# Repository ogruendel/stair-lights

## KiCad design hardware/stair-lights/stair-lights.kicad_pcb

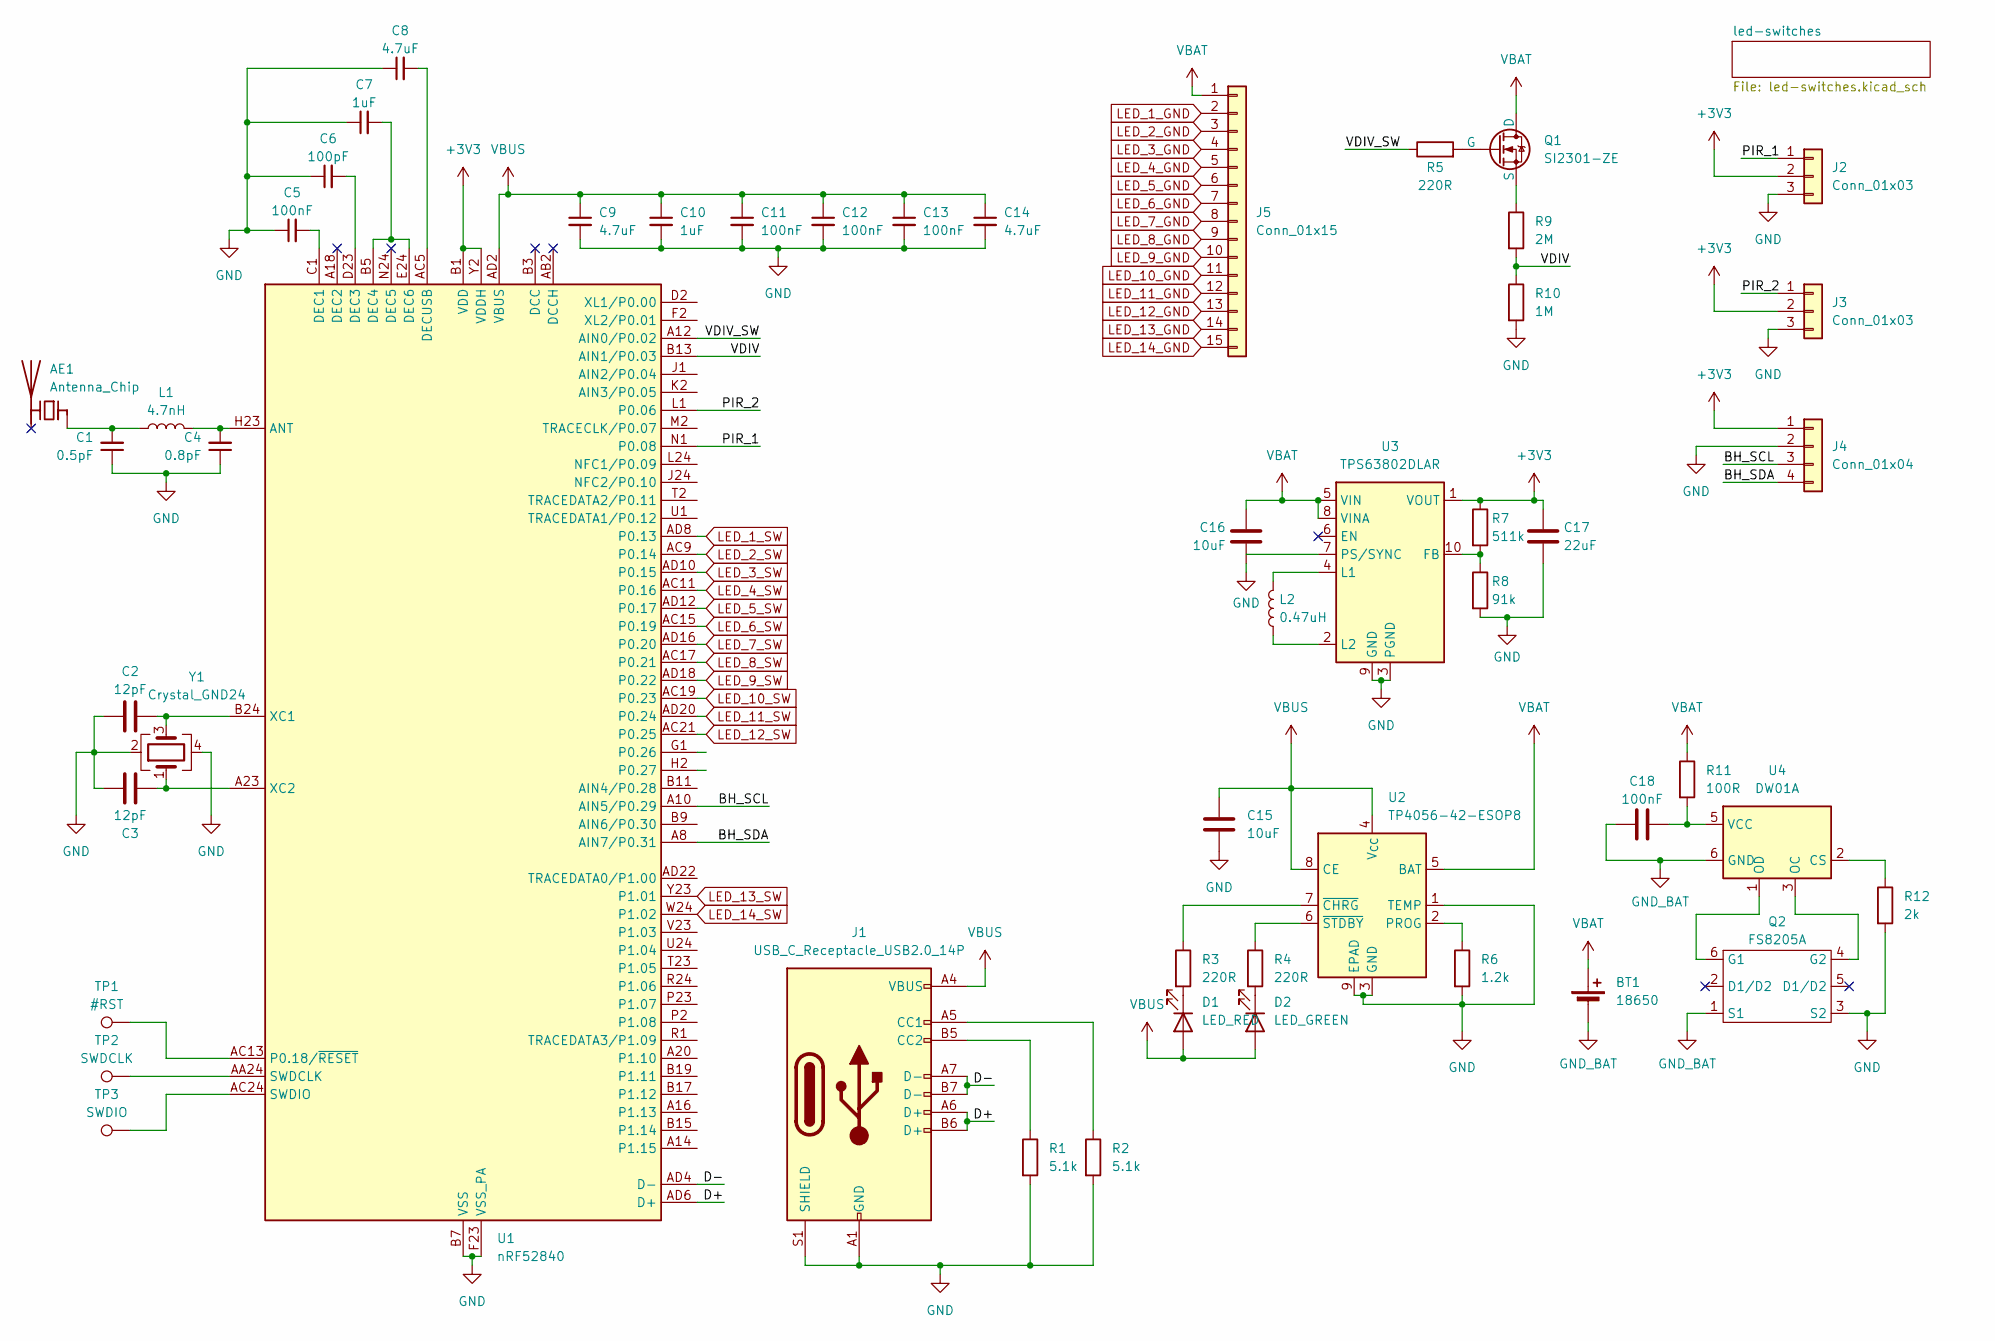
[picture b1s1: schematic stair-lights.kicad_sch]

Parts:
AE1: Antenna_Chip; L_1206_3216Metric; MPN C127629
BT1: 18650; BatteryHolder_Keystone_1042_1x18650; MPN C2988620
C1: 0.5pF; C_0402_1005Metric; MPN C285052
C2, C3: 12pF; C_0402_1005Metric; MPN C45359894
C4: 0.8pF; C_0402_1005Metric; MPN C41361068
C5, C11, C12, C13, C18: 100nF; C_0402_1005Metric; MPN C6119799
C6: 100pF; C_0402_1005Metric; MPN C77177
C7, C10: 1uF; C_0603_1608Metric; MPN C1592
C8, C9, C14: 4.7uF; C_0402_1005Metric; MPN C23733
C15, C16: 10uF; C_0603_1608Metric; MPN C6119842
C17: 22uF; C_0603_1608Metric; MPN C380323
D1: LED_RED; LED_1.7x1.1mm; MPN C965860
D2: LED_GREEN; LED_1.7x1.1mm; MPN C965863
J1: USB_C_Receptacle_USB2.0_14P; USB_C_Receptacle_GCT_USB4105-xx-A_16P_TopMnt_Horizontal; MPN C2765186
J2: Conn_01x03; JST_XH_S3B-XH-A_1x03_P2.50mm_Horizontal; MPN C157928
J3: Conn_01x03; JST_XH_B3B-XH-AM_1x03_P2.50mm_Vertical; MPN C161870
J4: Conn_01x04; JST_XH_B4B-XH-AM_1x04_P2.50mm_Vertical; MPN C161871
J5: Conn_01x15; JST_XH_S15B-XH-A_1x15_P2.50mm_Horizontal
L1: 4.7nH; L_0402_1005Metric; MPN C86065C86065
L2: 0.47uH; L_1008_2520Metric; MPN C5832368
Q1: SI2301-ZE; SOT-23; MPN C5261052
Q2: FS8205A; SOT-23-6; MPN C2830320
R1, R2: 5.1k; R_0603_1608Metric; MPN C26000
R3, R4, R5: 220R; R_0603_1608Metric; MPN C2907127
R6: 1.2k; R_0603_1608Metric; MPN C25987
R7: 511k; R_0402_1005Metric; MPN C5126239
R8: 91k; R_0402_1005Metric; MPN C4147
R9: 2M; R_0402_1005Metric; MPN C138014
R10: 1M; R_0402_1005Metric; MPN C26083
R11: 100R; R_0603_1608Metric; MPN C2907089
R12: 2k; R_0603_1608Metric; MPN C22975
TP1: #RST; TestPoint_Pad_D1.5mm
TP2: SWDCLK; TestPoint_Pad_D1.5mm
TP3: SWDIO; TestPoint_Pad_D1.5mm
U1: nRF52840; Nordic_AQFN-73-1EP_7x7mm_P0.5mm; MPN C190794
U2: TP4056-42-ESOP8; SOIC-8-1EP_3.9x4.9mm_P1.27mm_EP2.41x3.3mm_ThermalVias; MPN C7473158
U3: TPS63802DLAR; VSON-10; MPN C2845237
U4: DW01A; SOT-23-6; MPN C18164398
Y1: Crystal_GND24; Crystal_SMD_2016-4Pin_2.0x1.6mm; MPN C37635331

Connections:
+3V3: C17.2, J2.2, J3.2, J4.1, R7.1, U1.A22 (VDD), U1.AD14 (VDD), U1.AD23 (VDD), U1.B1 (VDD), U1.W1 (VDD), U1.Y2 (VDDH), U3.1 (VOUT)
/BH_SCL: J4.3, U1.A10 (AIN5/P0.29)
/BH_SDA: J4.4, U1.A8 (AIN7/P0.31)
/D+: J1.A6 (D+), J1.B6 (D+), U1.AD6 (D+)
/D-: J1.A7 (D-), J1.B7 (D-), U1.AD4 (D-)
/PIR_1: J2.1, U1.N1 (P0.08)
/PIR_2: J3.1, U1.L1 (P0.06)
/VDIV: R9.2, R10.1, U1.B13 (AIN1/P0.03)
/VDIV_SW: R5.1, U1.A12 (AIN0/P0.02)
GND: C1.1, C2.1, C3.1, C4.1, C5.1, C6.1, C7.1, C8.1, C9.2, C10.2, C11.2, C12.2, C13.2, C14.2, C15.2, C16.1, C17.1, J1.A1 (GND), J1.A12 (GND), J1.B1 (GND), J1.B12 (GND), J1.S1 (SHIELD), J2.3, J3.3, J4.2, Q2.3 (S2), R1.2, R2.2, R6.2, R8.2, R10.2, R12.2, U1.B7 (VSS), U1.EP (VSS), U1.F23 (VSS_PA), U2.1 (TEMP), U2.3 (GND), U2.9 (EPAD), U3.3 (PGND), U3.9 (GND), Y1.2, Y1.4; also elsewhere on the board
GND_BAT: BT1.2 (-), C18.1, Q2.1 (S1), U4.6 (GND)
LED_1_GND: J5.2; also elsewhere on the board
LED_1_SW: U1.AD8 (P0.13); also elsewhere on the board
LED_2_GND: J5.3; also elsewhere on the board
LED_2_SW: U1.AC9 (P0.14); also elsewhere on the board
LED_3_GND: J5.4; also elsewhere on the board
LED_3_SW: U1.AD10 (P0.15); also elsewhere on the board
LED_4_GND: J5.5; also elsewhere on the board
LED_4_SW: U1.AC11 (P0.16); also elsewhere on the board
LED_5_GND: J5.6; also elsewhere on the board
LED_5_SW: U1.AD12 (P0.17); also elsewhere on the board
LED_6_GND: J5.7; also elsewhere on the board
LED_6_SW: U1.AC15 (P0.19); also elsewhere on the board
LED_7_GND: J5.8; also elsewhere on the board
LED_7_SW: U1.AD16 (P0.20); also elsewhere on the board
LED_8_GND: J5.9; also elsewhere on the board
LED_8_SW: U1.AC17 (P0.21); also elsewhere on the board
LED_9_GND: J5.10; also elsewhere on the board
LED_9_SW: U1.AD18 (P0.22); also elsewhere on the board
LED_10_GND: J5.11; also elsewhere on the board
LED_10_SW: U1.AC19 (P0.23); also elsewhere on the board
LED_11_GND: J5.12; also elsewhere on the board
LED_11_SW: U1.AD20 (P0.24); also elsewhere on the board
LED_12_GND: J5.13; also elsewhere on the board
LED_12_SW: U1.AC21 (P0.25); also elsewhere on the board
LED_13_GND: J5.14; also elsewhere on the board
LED_13_SW: U1.Y23 (P1.01); also elsewhere on the board
LED_14_GND: J5.15; also elsewhere on the board
LED_14_SW: U1.W24 (P1.02); also elsewhere on the board
unnamed: AE1.1 (FEED), C1.2, L1.1
unnamed: D1.1 (K), R3.2
unnamed: D2.1 (K), R4.2
unnamed: J1.A5 (CC1), R2.1
unnamed: J1.B5 (CC2), R1.1
unnamed: Q1.1 (G), R5.2
unnamed: Q1.2 (S), R9.1
unnamed: Q2.6 (G1), U4.1 (OD)
unnamed: Q2.4 (G2), U4.3 (OC)
unnamed: C4.2, L1.2, U1.H23 (ANT)
unnamed: C5.2, U1.C1 (DEC1)
unnamed: C6.2, U1.D23 (DEC3)
unnamed: C7.2, U1.B5 (DEC4), U1.E24 (DEC6)
unnamed: C8.2, U1.AC5 (DECUSB)
unnamed: TP1.1, U1.AC13 (P0.18/~RESET)
unnamed: TP2.1, U1.AA24 (SWDCLK)
unnamed: TP3.1, U1.AC24 (SWDIO)
unnamed: C2.2, U1.B24 (XC1), Y1.3
unnamed: C3.2, U1.A23 (XC2), Y1.1
unnamed: R6.1, U2.2 (PROG)
unnamed: R3.1, U2.7 (~CHRG)
unnamed: R4.1, U2.6 (~STDBY)
unnamed: R7.2, R8.1, U3.10 (FB)
unnamed: L2.2, U3.4 (L1)
unnamed: L2.1, U3.2 (L2)
unnamed: R12.1, U4.2 (CS)
unnamed: C18.2, R11.2, U4.5 (VCC)
VBAT: BT1.1 (+), C16.2, J5.1, Q1.3 (D), R11.1, U2.5 (BAT), U3.5 (VIN), U3.8 (VINA)
VBUS: C9.1, C10.1, C11.1, C12.1, C13.1, C14.1, C15.1, D1.2 (A), D2.2 (A), J1.A4 (VBUS), J1.A9 (VBUS), J1.B4 (VBUS), J1.B9 (VBUS), U1.AD2 (VBUS), U2.4 (V_{CC}), U2.8 (CE)

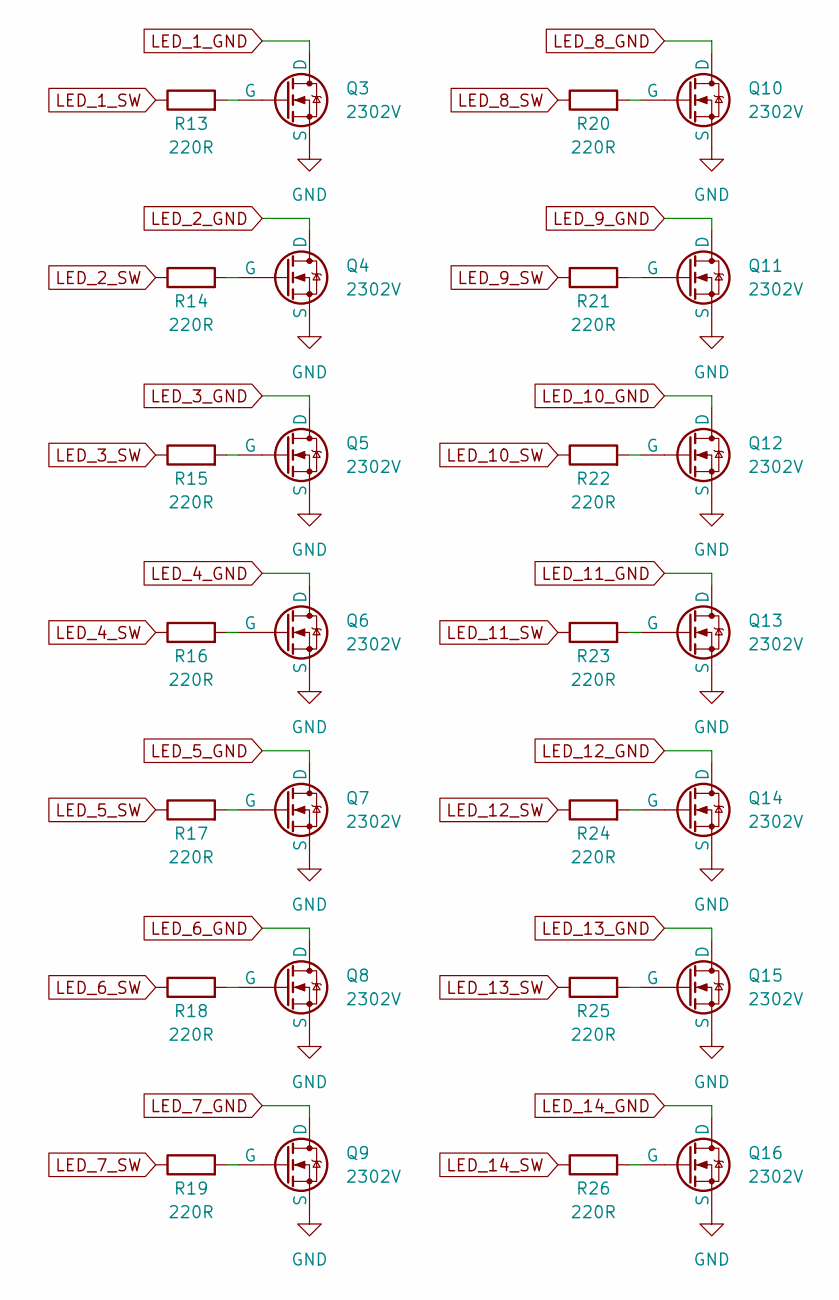
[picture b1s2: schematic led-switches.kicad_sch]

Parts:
Q3, Q4, Q5, Q6, Q7, Q8, Q9, Q10, Q11, Q12, Q13, Q14, Q15, Q16: 2302V; SOT-23; MPN C7431443
R13, R14, R15, R16, R17, R18, R19, R20, R21, R22, R23, R24, R25, R26: 220R; R_0603_1608Metric; MPN C2907127

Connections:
GND: Q3.2 (S), Q4.2 (S), Q5.2 (S), Q6.2 (S), Q7.2 (S), Q8.2 (S), Q9.2 (S), Q10.2 (S), Q11.2 (S), Q12.2 (S), Q13.2 (S), Q14.2 (S), Q15.2 (S), Q16.2 (S); also elsewhere on the board
LED_1_GND: Q3.3 (D); also elsewhere on the board
LED_1_SW: R13.1; also elsewhere on the board
LED_2_GND: Q4.3 (D); also elsewhere on the board
LED_2_SW: R14.1; also elsewhere on the board
LED_3_GND: Q5.3 (D); also elsewhere on the board
LED_3_SW: R15.1; also elsewhere on the board
LED_4_GND: Q6.3 (D); also elsewhere on the board
LED_4_SW: R16.1; also elsewhere on the board
LED_5_GND: Q7.3 (D); also elsewhere on the board
LED_5_SW: R17.1; also elsewhere on the board
LED_6_GND: Q8.3 (D); also elsewhere on the board
LED_6_SW: R18.1; also elsewhere on the board
LED_7_GND: Q9.3 (D); also elsewhere on the board
LED_7_SW: R19.1; also elsewhere on the board
LED_8_GND: Q10.3 (D); also elsewhere on the board
LED_8_SW: R20.1; also elsewhere on the board
LED_9_GND: Q11.3 (D); also elsewhere on the board
LED_9_SW: R21.1; also elsewhere on the board
LED_10_GND: Q12.3 (D); also elsewhere on the board
LED_10_SW: R22.1; also elsewhere on the board
LED_11_GND: Q13.3 (D); also elsewhere on the board
LED_11_SW: R23.1; also elsewhere on the board
LED_12_GND: Q14.3 (D); also elsewhere on the board
LED_12_SW: R24.1; also elsewhere on the board
LED_13_GND: Q15.3 (D); also elsewhere on the board
LED_13_SW: R25.1; also elsewhere on the board
LED_14_GND: Q16.3 (D); also elsewhere on the board
LED_14_SW: R26.1; also elsewhere on the board
unnamed: Q3.1 (G), R13.2
unnamed: Q4.1 (G), R14.2
unnamed: Q5.1 (G), R15.2
unnamed: Q6.1 (G), R16.2
unnamed: Q7.1 (G), R17.2
unnamed: Q8.1 (G), R18.2
unnamed: Q9.1 (G), R19.2
unnamed: Q10.1 (G), R20.2
unnamed: Q11.1 (G), R21.2
unnamed: Q12.1 (G), R22.2
unnamed: Q13.1 (G), R23.2
unnamed: Q14.1 (G), R24.2
unnamed: Q15.1 (G), R25.2
unnamed: Q16.1 (G), R26.2

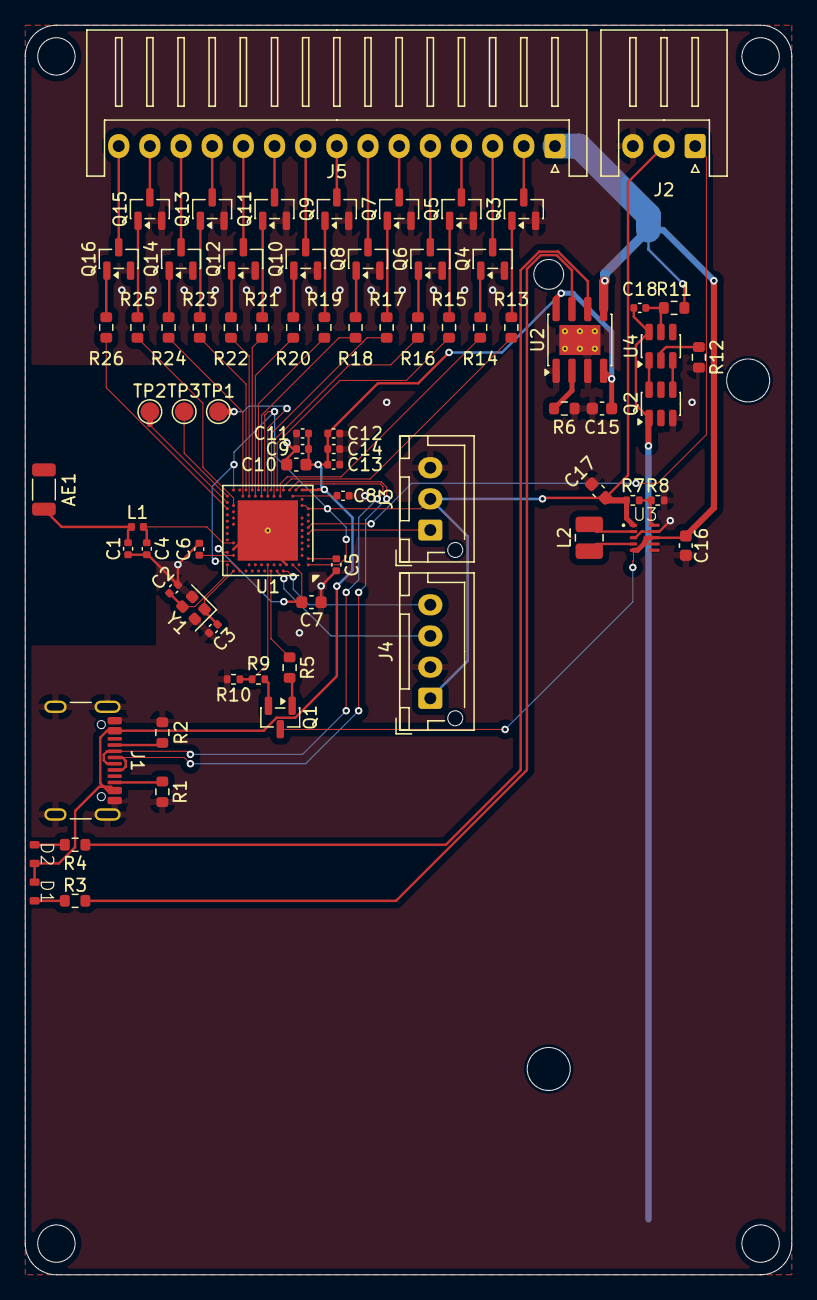
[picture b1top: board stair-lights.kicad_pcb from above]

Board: 2 copper layers, 61.5 x 100.2 mm, 79 parts (1 on the bottom side), 82 nets.

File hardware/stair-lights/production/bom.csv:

Designator,Footprint,Quantity,Value,LCSC Part #
,,1,,
AE1,1206,1,Antenna_Chip,
BT1,BatteryHolder_Keystone_1042_1x18650,1,18650,C2988620
C1,0402,1,0.5pF,
"C10, C7",0603,2,1uF,C1592
"C11, C12, C13, C18, C5",0402,5,100nF,C6119799
"C14, C8, C9",0402,3,4.7uF,C23733
"C15, C16",0603,2,10uF,C6119842
C17,0603,1,22uF,C380323
"C2, C3",0402,2,12pF,C45359894
C4,0402,1,0.8pF,
C6,0402,1,100pF,C77177
D1,LED_1.7x1.1mm,1,LED_RED,C965860
D2,LED_1.7x1.1mm,1,LED_GREEN,C965863
J1,USB_C_Receptacle_GCT_USB4105-xx-A_16P_TopMnt_Horizontal,1,USB_C_Receptacle_USB2.0_14P,C2765186
J2,JST_XH_S3B-XH-A_1x03_P2.50mm_Horizontal,1,Conn_01x03,C157928
J3,JST_XH_B3B-XH-AM_1x03_P2.50mm_Vertical,1,Conn_01x03,C161870
J4,JST_XH_B4B-XH-AM_1x04_P2.50mm_Vertical,1,Conn_01x04,C161871
J5,JST_XH_S15B-XH-A_1x15_P2.50mm_Horizontal,1,Conn_01x15,
L1,0402,1,4.7nH,
L2,1008,1,0.47uH,C5832368
Q1,SOT-23,1,SI2301-ZE,C5261052
"Q10, Q11, Q12, Q13, Q14, Q15, Q16, Q3, Q4, Q5, Q6, Q7, Q8, Q9",SOT-23,14,2302V,C7431443
Q2,SOT-23-6,1,FS8205A,C2830320
"R1, R2",0603,2,5.1k,C26000
R10,0402,1,1M,C26083
R11,0603,1,100R,C2907089
R12,0603,1,2k,C22975
"R13, R14, R15, R16, R17, R18, R19, R20, R21, R22, R23, R24, R25, R26, R3, R4, R5",0603,17,220R,C2907127
R6,0603,1,1.2k,C25987
R7,0402,1,511k,C5126239
R8,0402,1,91k,C4147
R9,0402,1,2M,C138014
TP1,TestPoint_Pad_D1.5mm,1,#RST,
TP2,TestPoint_Pad_D1.5mm,1,SWDCLK,
TP3,TestPoint_Pad_D1.5mm,1,SWDIO,
U1,Nordic_AQFN-73-1EP_7x7mm_P0.5mm,1,nRF52840,C190794
U2,SOIC-8-1EP_3.9x4.9mm_P1.27mm_EP2.41x3.3mm_ThermalVias,1,TP4056-42-ESOP8,C7473158
U3,VSON-10,1,TPS63802DLAR,C2845237
U4,SOT-23-6,1,DW01A,C18164398
Y1,Crystal_SMD_2016-4Pin_2.0x1.6mm,1,Crystal_GND24,C37635331

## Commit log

2025-10-21 chore: remove unwanted files
